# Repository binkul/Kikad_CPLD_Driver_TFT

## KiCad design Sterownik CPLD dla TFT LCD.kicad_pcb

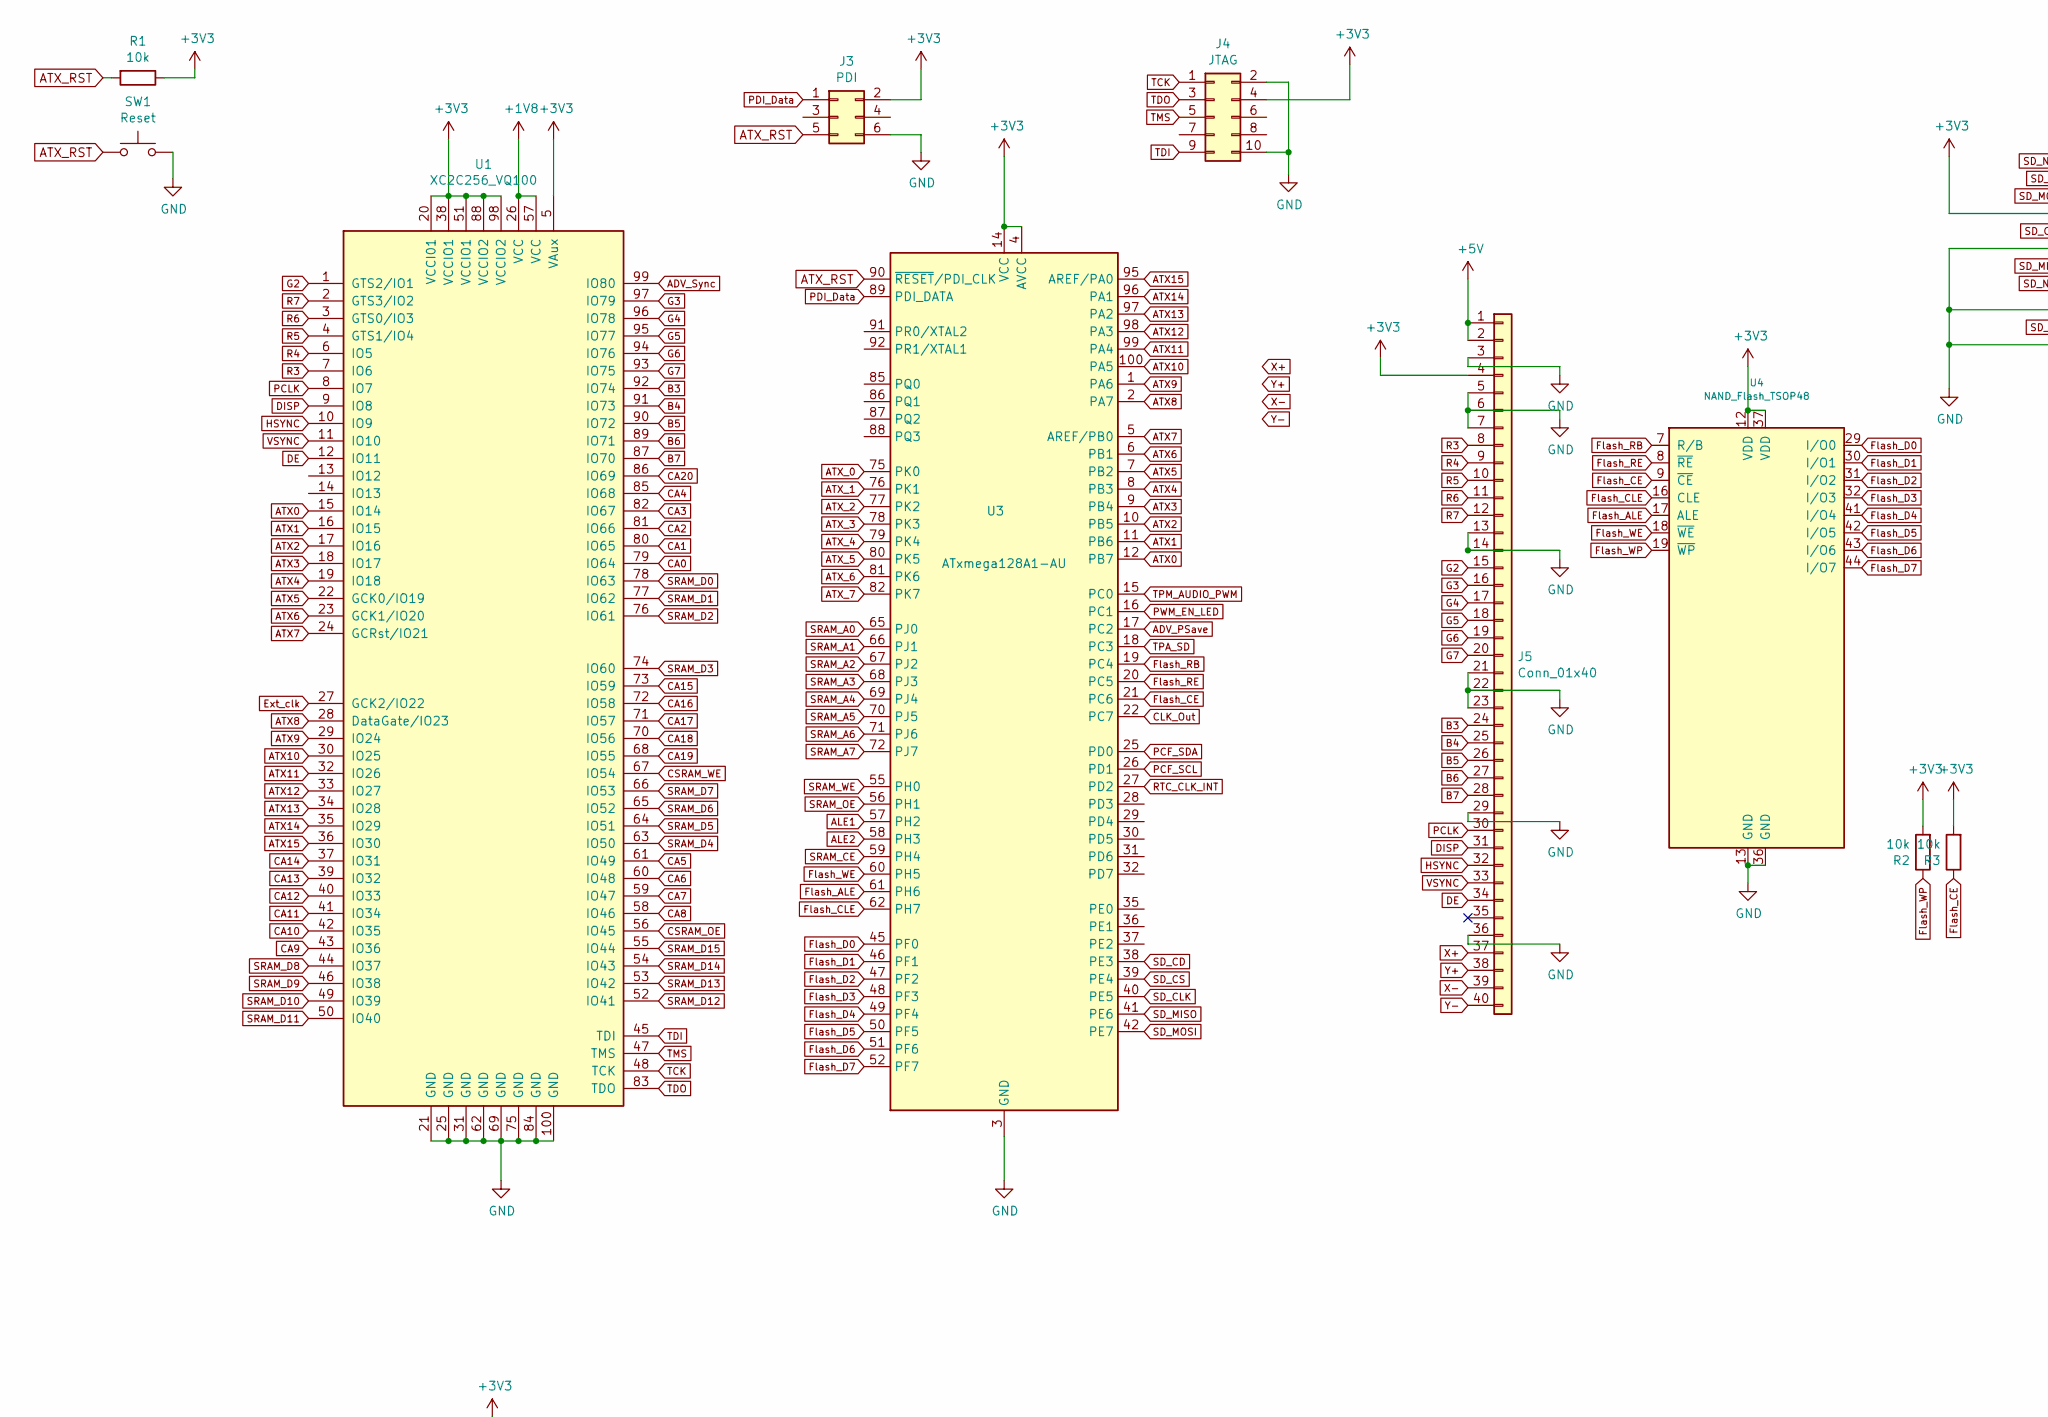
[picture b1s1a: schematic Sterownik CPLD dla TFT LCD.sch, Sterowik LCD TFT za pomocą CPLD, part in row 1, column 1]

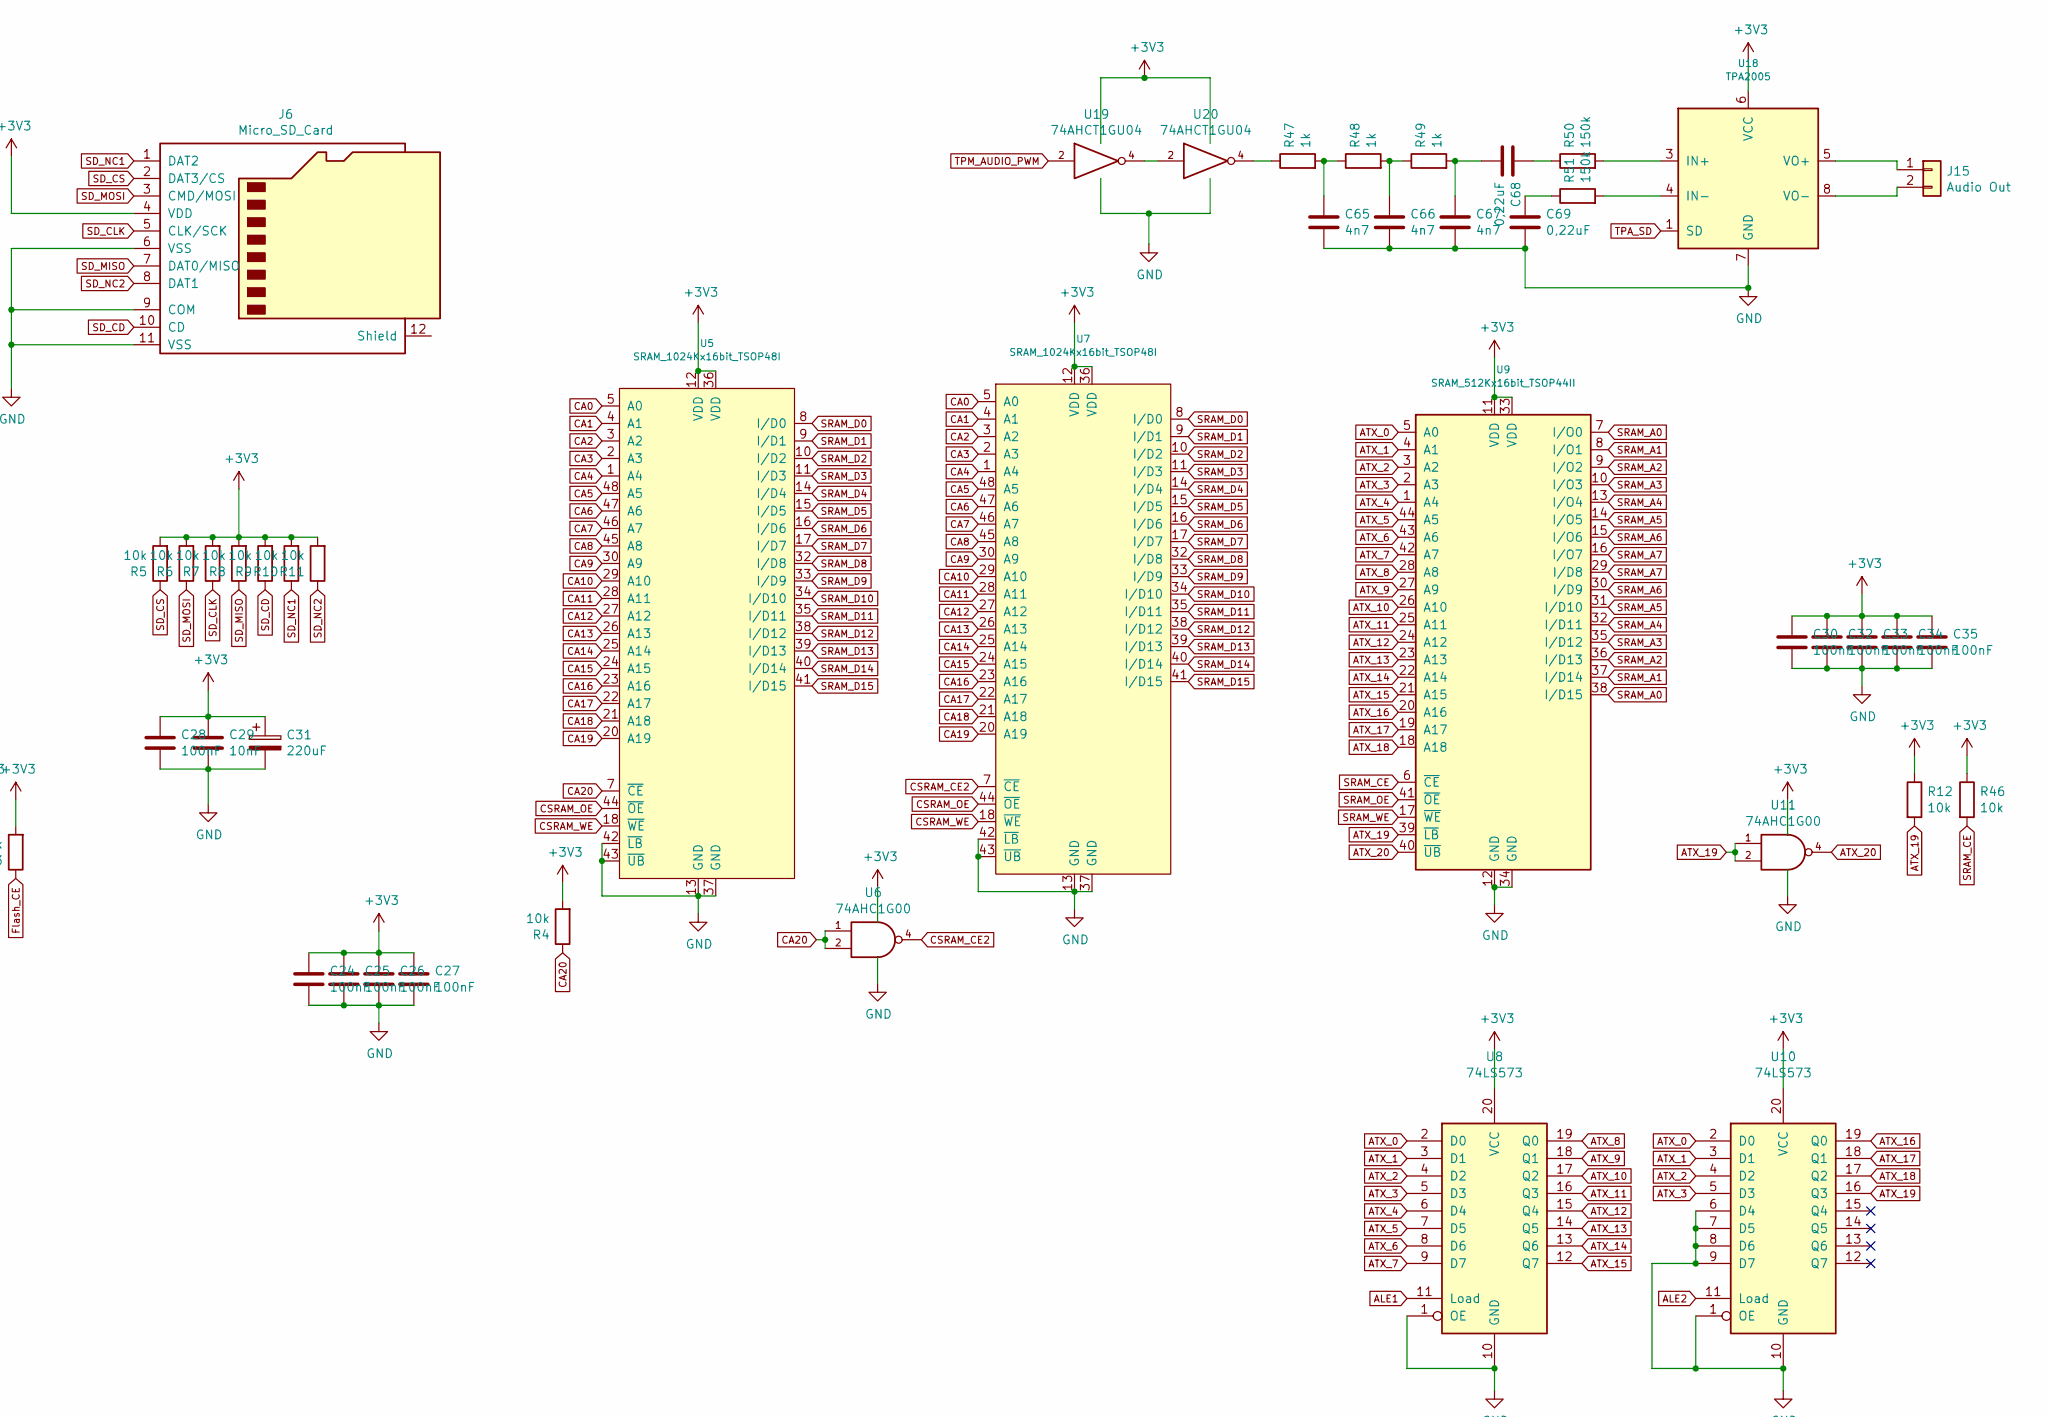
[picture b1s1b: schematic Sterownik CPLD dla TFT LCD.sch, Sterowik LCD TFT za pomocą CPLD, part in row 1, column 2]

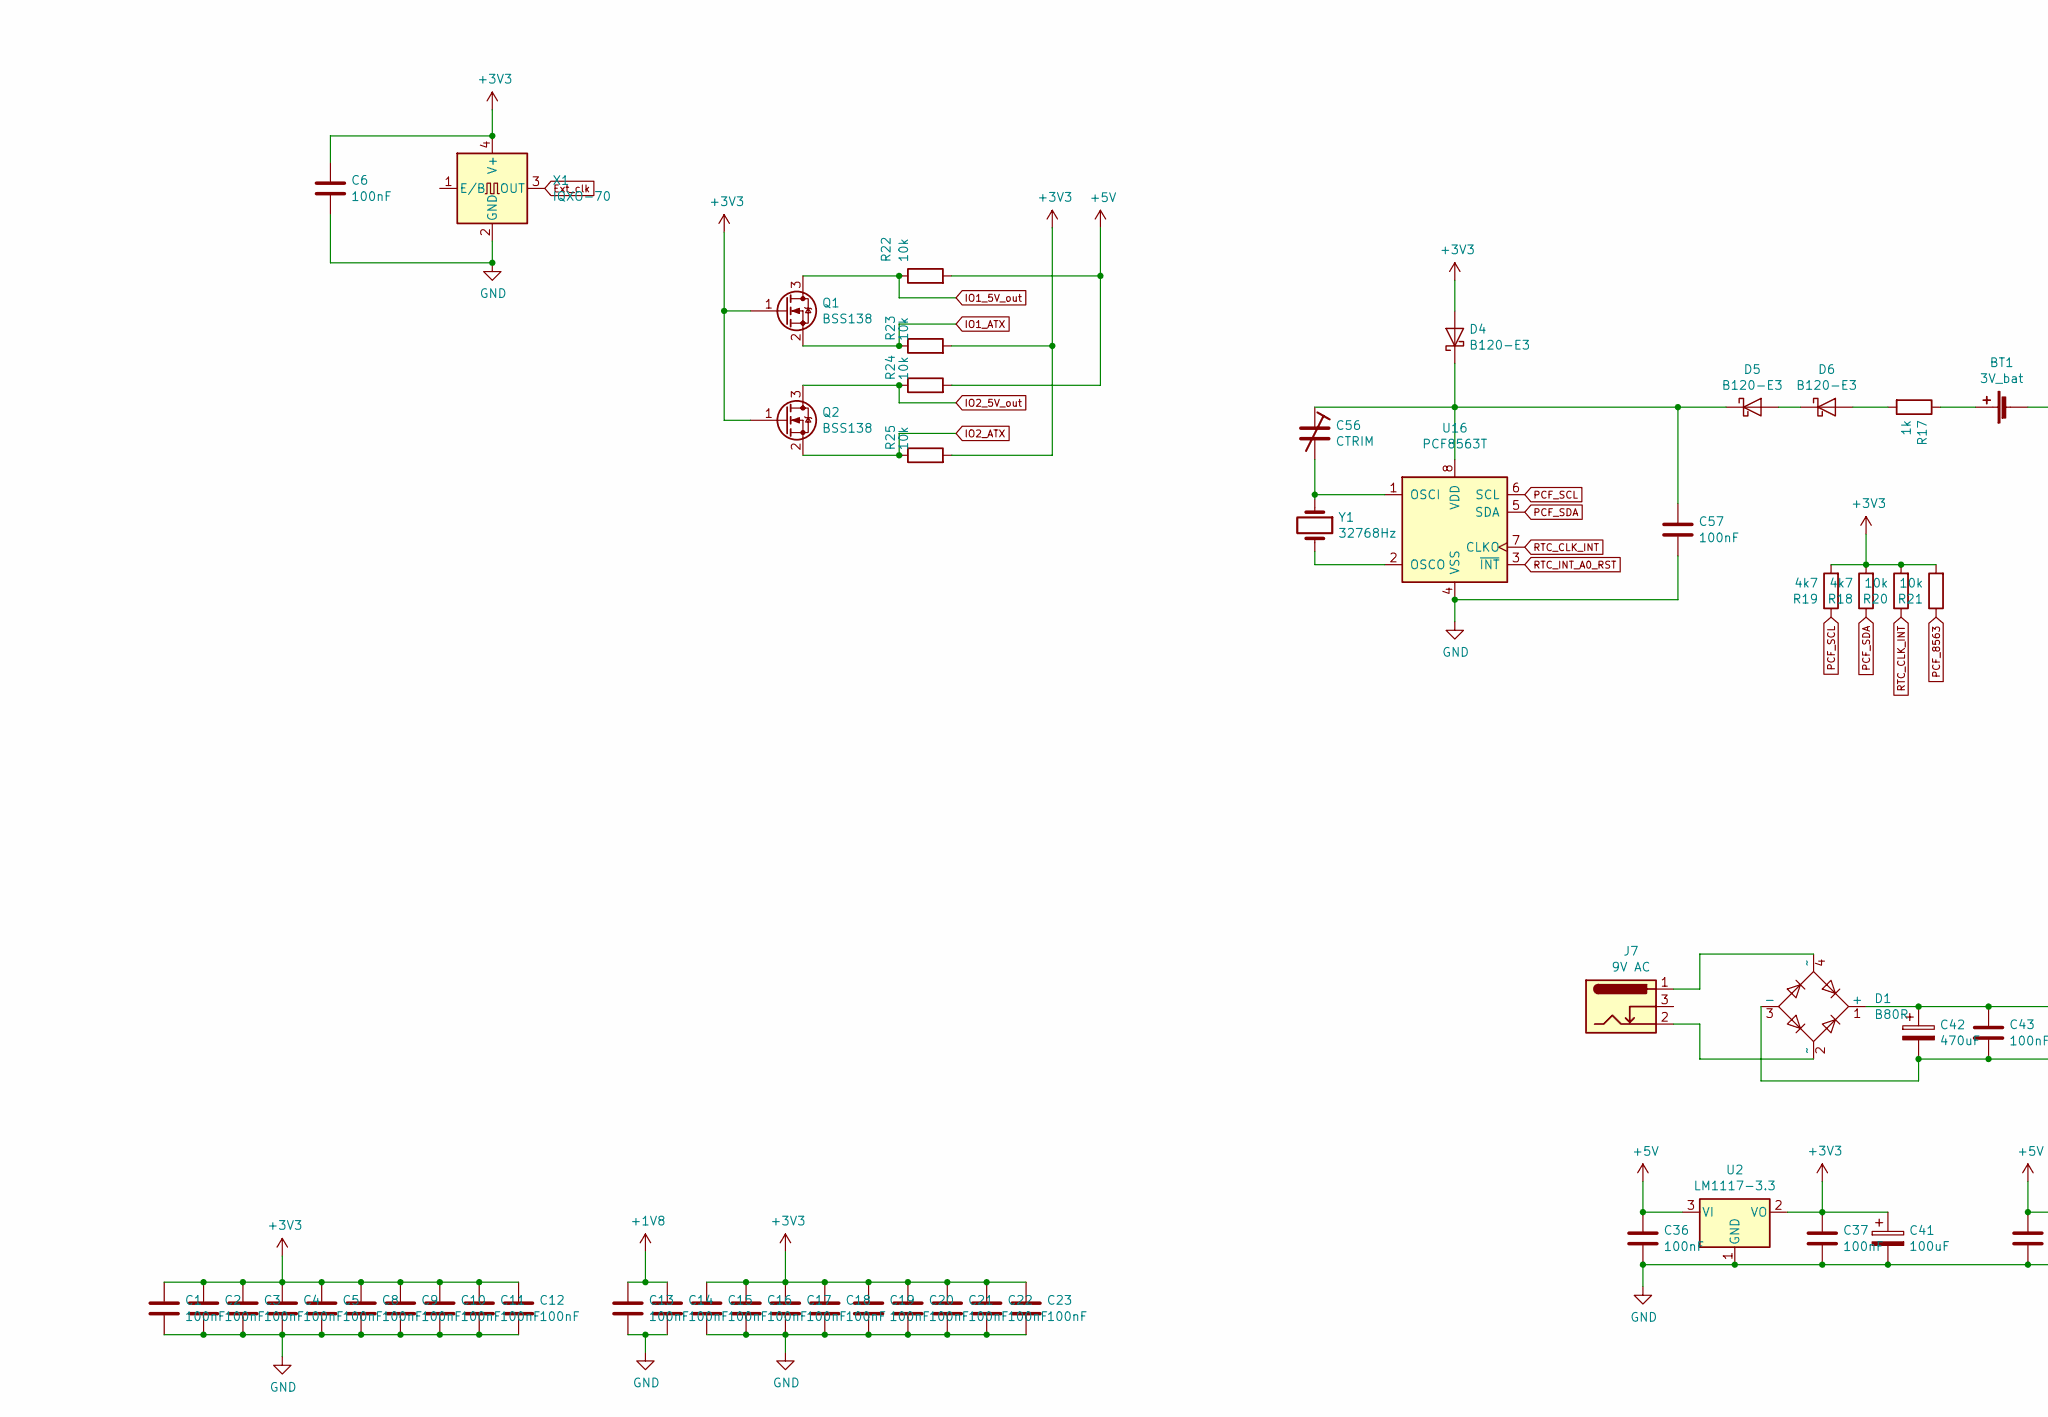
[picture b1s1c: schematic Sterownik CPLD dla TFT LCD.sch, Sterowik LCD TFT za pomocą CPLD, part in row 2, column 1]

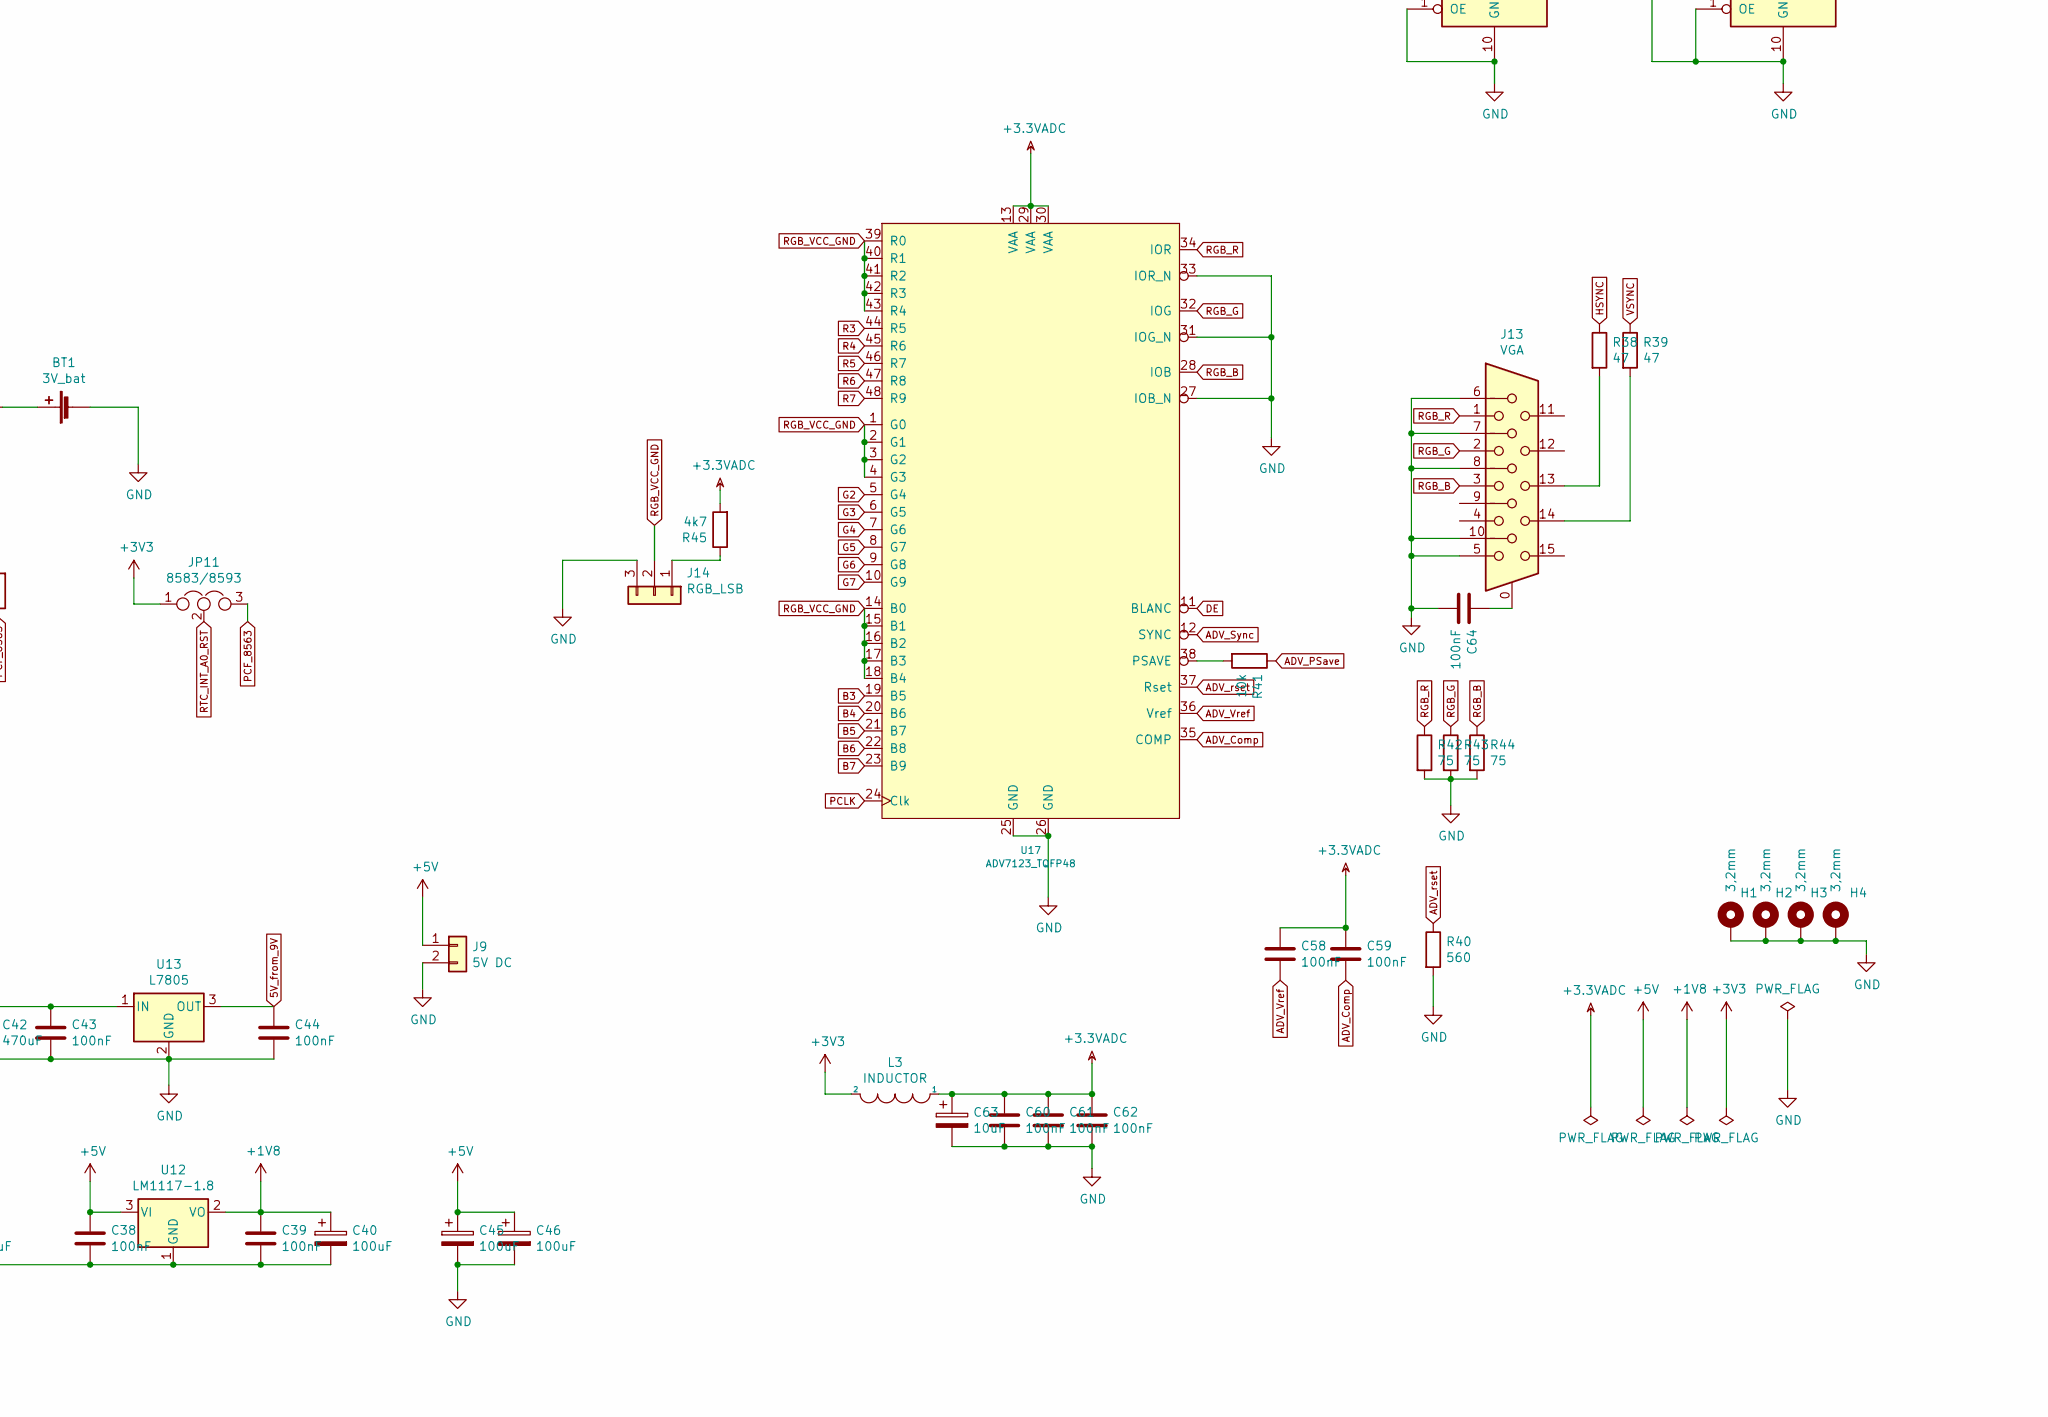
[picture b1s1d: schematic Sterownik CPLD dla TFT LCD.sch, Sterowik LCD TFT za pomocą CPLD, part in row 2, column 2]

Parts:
BT1: 3V_bat; BatteryHolder_CR1220
C1, C2, C3, C4, C5, C8, C9, C10, C11, C12, C13, C14, C15, C16, C17, C18, C19, C20, C21, C22, C23, C24, C25, C26, C27, C28, C30, C32, C33, C34, C35, C57, C58, C59, C60, C61, C62, C64: 100nF; C_0603_1608Metric
C6, C36, C37, C38, C39, C43, C44: 100nF; C_1206_3216Metric
C29: 10nF; C_0603_1608Metric
C31: 220uF; CP_EIA-7343-40_Kemet-Y_Pad2.25x2.55mm_HandSolder
C40, C41, C45, C46: 100uF; CP_Elec_6.3x5.9
C42: 470uF; CP_Radial_D10.0mm_P5.00mm
C56: CTRIM; C_Trimmer_Murata_TZW4
C63: 10uF; CP_Elec_4x3
C65, C66, C67: 4n7; C_0603_1608Metric
C68, C69: 0,22uF; C_1206_3216Metric
D1: B80R; Diode_Bridge_Round_D9.0mm
D4, D5, D6: B120-E3; D_1206_3216Metric
H1, H2, H3, H4: 3,2mm; MountingHole_3.2mm_M3_Pad
J3: PDI; IDC-Header_2x03_P2.54mm_Vertical
J4: JTAG; IDC-Header_2x05_P2.54mm_Vertical
J5: Conn_01x40; Hirose_FH12-40S-0.5SH_1x40-1MP_P0.50mm_Horizontal
J6: Micro_SD_Card; MCC SDMicro
J7: 9V AC; DC_Jack_14mm
J9: 5V DC; Zlacze_srubowe_2x_5mm
J13: VGA; DSUB-15-HD_Female_Horizontal_P2.29x1.98mm_EdgePinOffset8.35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
J14: RGB_LSB; PinHeader_1x03_P2.54mm_Vertical
J15: Audio Out; PinSocket_1x02_P2.54mm_Vertical
JP11: 8583/8593; SolderJumper-3_P1.3mm_Open_RoundedPad1.0x1.5mm
L3: INDUCTOR; L_0805_2012Metric
Q1, Q2: BSS138; SOT-23
R1, R2, R3, R4, R5, R6, R7, R8, R9, R10, R11, R12, R22, R23, R24, R25, R46: 10k; R_0603_1608Metric
R17: 1k; R_1206_3216Metric
R18, R19, R45: 4k7; R_1206_3216Metric
R20, R21: 10k; R_1206_3216Metric
R38, R39: 47; R_0805_2012Metric
R40: 560; R_0805_2012Metric
R41: 10k; R_0805_2012Metric
R42, R43, R44: 75; R_0805_2012Metric
R47, R48, R49: 1k; R_0603_1608Metric
R50, R51: 150k; R_1206_3216Metric
SW1: Reset; MicroSwitch
U1: XC2C256_VQ100; VQFP-100_14x14mm_P0.5mm
U2: LM1117-3.3; TO-252-2
U3: ATxmega128A1-AU; TQFP-100_14x14mm_P0.5mm
U4: NAND_Flash_TSOP48; TSOP-I-48_18.4x12mm_P0.5mm
U5, U7: SRAM_1024Kx16bit_TSOP48I; TSOP-I-48_18.4x12mm_P0.5mm
U6, U11: 74AHC1G00; SOT-23-5
U8, U10: 74LS573; SSOP-20_5.3x7.2mm_P0.65mm
U9: SRAM_512Kx16bit_TSOP44II; TSOP-II-44_10.16x18.41mm_P0.8mm
U12: LM1117-1.8; TO-252-2
U13: L7805; TO-263-2
U16: PCF8563T; SO-8_3.9x4.9mm_P1.27mm
U17: ADV7123_TQFP48; TQFP-48_7x7mm_P0.5mm
U18: TPA2005; MSOP8
U19, U20: 74AHCT1GU04; SOT-23-5
X1: IQXO-70; Oscillator_SMD_IQD_IQXO70-4Pin_7.5x5.0mm
Y1: 32768Hz; Crystal_C26-LF_D2.1mm_L6.5mm_Horizontal

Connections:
5V_from_9V: C44.1, U13.3 (OUT)
+1V8: C13.1, C14.1, C39.1, C40.1, U1.26 (VCC), U1.57 (VCC), U12.2 (VO)
+3.3VADC: C58.1, C59.1, C60.1, C61.1, C62.1, C63.1, L3.1, R45.2, U17.13 (VAA), U17.29 (VAA), U17.30 (VAA)
+3V3: C1.1, C2.1, C3.1, C4.1, C5.1, C6.1, C8.1, C9.1, C10.1, C11.1, C12.1, C15.1, C16.1, C17.1, C18.1, C19.1, C20.1, C21.1, C22.1, C23.1, C24.1, C25.1, C26.1, C27.1, C28.1, C29.1, C30.1, C31.1, C32.1, C33.1, C34.1, C35.1, C37.1, C41.1, D4.2 (A), J3.2, J4.4, J5.4, J6.4 (VDD), JP11.1, L3.2, Q1.1 (G), Q2.1 (G), R1.1, R2.2, R3.2, R4.2, R5.2, R6.2, R7.2, R8.2, R9.2, R10.2, R11.2, R12.1, R18.2, R19.2, R20.2, R21.2, R23.2, R25.2, R46.1, U1.5 (VAux), U1.20 (VCCI01), U1.38 (VCCIO1), U1.51 (VCCIO1), U1.88 (VCCIO2), U1.98 (VCCIO2), U2.2 (VO), U3.4 (AVCC), U3.14 (VCC), U3.24 (VCC), U3.34 (VCC), U3.44 (VCC), U3.54 (VCC), U3.64 (VCC), U3.74 (VCC), U3.83 (VCC), U3.94 (AVCC), U4.12 (VDD), U4.37 (VDD), U5.12 (VDD), U5.36 (VDD), U6.5 (VCC), U7.12 (VDD), U7.36 (VDD), U8.20 (VCC), U9.11 (VDD), U9.33 (VDD), U10.20 (VCC), U11.5 (VCC), U18.6 (VCC), U19.5 (VCC), U20.5 (VCC), X1.4 (V+)
+5V: C36.1, C38.1, C45.1, C46.1, J5.1, J5.2, J9.1, R22.2, R24.2, U2.3 (VI), U12.3 (VI)
ADV_Comp: C59.2, U17.35 (COMP)
ADV_PSave: R41.1, U3.17 (PC2)
ADV_Sync: U1.99 (IO80), U17.12 (SYNC)
ADV_Vref: C58.2, U17.36 (Vref)
ADV_rset: R40.1, U17.37 (Rset)
ALE1: U3.57 (PH2), U8.11 (Load)
ALE2: U3.58 (PH3), U10.11 (Load)
ATX0: U1.15 (IO14), U3.12 (PB7)
ATX1: U1.16 (IO15), U3.11 (PB6)
ATX2: U1.17 (IO16), U3.10 (PB5)
ATX3: U1.18 (IO17), U3.9 (PB4)
ATX4: U1.19 (IO18), U3.8 (PB3)
ATX5: U1.22 (GCK0/IO19), U3.7 (PB2)
ATX6: U1.23 (GCK1/IO20), U3.6 (PB1)
ATX7: U1.24 (GCRst/IO21), U3.5 (AREF/PB0)
ATX8: U1.28 (DataGate/IO23), U3.2 (PA7)
ATX9: U1.29 (IO24), U3.1 (PA6)
ATX10: U1.30 (IO25), U3.100 (PA5)
ATX11: U1.32 (IO26), U3.99 (PA4)
ATX12: U1.33 (IO27), U3.98 (PA3)
ATX13: U1.34 (IO28), U3.97 (PA2)
ATX14: U1.35 (IO29), U3.96 (PA1)
ATX15: U1.36 (IO30), U3.95 (AREF/PA0)
ATX_0: U3.75 (PK0), U8.2 (D0), U9.5 (A0), U10.2 (D0)
ATX_1: U3.76 (PK1), U8.3 (D1), U9.4 (A1), U10.3 (D1)
ATX_2: U3.77 (PK2), U8.4 (D2), U9.3 (A2), U10.4 (D2)
ATX_3: U3.78 (PK3), U8.5 (D3), U9.2 (A3), U10.5 (D3)
ATX_4: U3.79 (PK4), U8.6 (D4), U9.1 (A4)
ATX_5: U3.80 (PK5), U8.7 (D5), U9.44 (A5)
ATX_6: U3.81 (PK6), U8.8 (D6), U9.43 (A6)
ATX_7: U3.82 (PK7), U8.9 (D7), U9.42 (A7)
ATX_8: U8.19 (Q0), U9.28 (A8)
ATX_9: U8.18 (Q1), U9.27 (A9)
ATX_10: U8.17 (Q2), U9.26 (A10)
ATX_11: U8.16 (Q3), U9.25 (A11)
ATX_12: U8.15 (Q4), U9.24 (A12)
ATX_13: U8.14 (Q5), U9.23 (A13)
ATX_14: U8.13 (Q6), U9.22 (A14)
ATX_15: U8.12 (Q7), U9.21 (A15)
ATX_16: U9.20 (A16), U10.19 (Q0)
ATX_17: U9.19 (A17), U10.18 (Q1)
ATX_18: U9.18 (A18), U10.17 (Q2)
ATX_19: R12.2, U9.39 (~LB), U10.16 (Q3), U11.1, U11.2
ATX_20: U9.40 (~UB), U11.4
ATX_RST: J3.5, R1.2, SW1.1, U3.90 (~RESET~/PDI_CLK)
B3: J5.24, U1.92 (IO74), U17.19 (B5)
B4: J5.25, U1.91 (IO73), U17.20 (B6)
B5: J5.26, U1.90 (IO72), U17.21 (B7)
B6: J5.27, U1.89 (IO71), U17.22 (B8)
B7: J5.28, U1.87 (IO70), U17.23 (B9)
CA0: U1.79 (IO64), U5.5 (A0), U7.5 (A0)
CA1: U1.80 (IO65), U5.4 (A1), U7.4 (A1)
CA2: U1.81 (IO66), U5.3 (A2), U7.3 (A2)
CA3: U1.82 (IO67), U5.2 (A3), U7.2 (A3)
CA4: U1.85 (IO68), U5.1 (A4), U7.1 (A4)
CA5: U1.61 (IO49), U5.48 (A5), U7.48 (A5)
CA6: U1.60 (IO48), U5.47 (A6), U7.47 (A6)
CA7: U1.59 (IO47), U5.46 (A7), U7.46 (A7)
CA8: U1.58 (IO46), U5.45 (A8), U7.45 (A8)
CA9: U1.43 (IO36), U5.30 (A9), U7.30 (A9)
CA10: U1.42 (IO35), U5.29 (A10), U7.29 (A10)
CA11: U1.41 (IO34), U5.28 (A11), U7.28 (A11)
CA12: U1.40 (IO33), U5.27 (A12), U7.27 (A12)
CA13: U1.39 (IO32), U5.26 (A13), U7.26 (A13)
CA14: U1.37 (IO31), U5.25 (A14), U7.25 (A14)
CA15: U1.73 (IO59), U5.24 (A15), U7.24 (A15)
CA16: U1.72 (IO58), U5.23 (A16), U7.23 (A16)
CA17: U1.71 (IO57), U5.22 (A17), U7.22 (A17)
CA18: U1.70 (IO56), U5.21 (A18), U7.21 (A18)
CA19: U1.68 (IO55), U5.20 (A19), U7.20 (A19)
CA20: R4.1, U1.86 (IO69), U5.7 (~CE), U6.1, U6.2
CSRAM_CE2: U6.4, U7.7 (~CE)
CSRAM_OE: U1.56 (IO45), U5.44 (~OE), U7.44 (~OE)
CSRAM_WE: U1.67 (IO54), U5.18 (~WE), U7.18 (~WE)
DE: J5.34, U1.12 (IO11), U17.11 (BLANC)
DISP: J5.31, U1.9 (IO8)
Ext_clk: U1.27 (GCK2/IO22), X1.3 (OUT)
Flash_ALE: U3.61 (PH6), U4.17 (ALE)
Flash_CE: R3.1, U3.21 (PC6), U4.9 (~CE)
Flash_CLE: U3.62 (PH7), U4.16 (CLE)
Flash_D0: U3.45 (PF0), U4.29 (I/O0)
Flash_D1: U3.46 (PF1), U4.30 (I/O1)
Flash_D2: U3.47 (PF2), U4.31 (I/O2)
Flash_D3: U3.48 (PF3), U4.32 (I/O3)
Flash_D4: U3.49 (PF4), U4.41 (I/O4)
Flash_D5: U3.50 (PF5), U4.42 (I/O5)
Flash_D6: U3.51 (PF6), U4.43 (I/O6)
Flash_D7: U3.52 (PF7), U4.44 (I/O7)
Flash_RB: U3.19 (PC4), U4.7 (R/B)
Flash_RE: U3.20 (PC5), U4.8 (~RE)
Flash_WE: U3.60 (PH5), U4.18 (~WE)
Flash_WP: R2.1, U4.19 (~WP)
G2: J5.15, U1.1 (GTS2/IO1), U17.5 (G4)
G3: J5.16, U1.97 (IO79), U17.6 (G5)
G4: J5.17, U1.96 (IO78), U17.7 (G6)
G5: J5.18, U1.95 (IO77), U17.8 (G7)
G6: J5.19, U1.94 (IO76), U17.9 (G8)
G7: J5.20, U1.93 (IO75), U17.10 (G9)
GND: BT1.2 (-), C1.2, C2.2, C3.2, C4.2, C5.2, C6.2, C8.2, C9.2, C10.2, C11.2, C12.2, C13.2, C14.2, C15.2, C16.2, C17.2, C18.2, C19.2, C20.2, C21.2, C22.2, C23.2, C24.2, C25.2, C26.2, C27.2, C28.2, C29.2, C30.2, C31.2, C32.2, C33.2, C34.2, C35.2, C36.2, C37.2, C38.2, C39.2, C40.2, C41.2, C42.2, C43.2, C44.2, C45.2, C46.2, C57.2, C60.2, C61.2, C62.2, C63.2, C64.2, C65.2, C66.2, C67.2, C69.2, D1.3 (-), H1.1, H2.1, H3.1, H4.1, J3.6, J4.2, J4.10, J5.3, J5.5, J5.6, J5.7, J5.13, J5.14, J5.21, J5.22, J5.23, J5.29, J5.36, J6.6 (VSS), J6.9 (COM), J6.11 (VSS), J9.2, J13.5, J13.6, J13.7, J13.8, J13.10, J14.3, R40.2, R42.2, R43.2, R44.2, SW1.2, U1.21 (GND), U1.25 (GND), U1.31 (GND), U1.62 (GND), U1.69 (GND), U1.75 (GND), U1.84 (GND), U1.100 (GND), U2.1 (GND), U3.3 (GND), U3.13 (GND), U3.23 (GND), U3.33 (GND), U3.43 (GND), U3.53 (GND), U3.63 (GND), U3.73 (GND), U3.84 (GND), U3.93 (GND), U4.13 (GND), U4.36 (GND), U5.13 (GND), U5.37 (GND), U5.42 (~LB), U5.43 (~UB), U6.3 (GND), U7.13 (GND), U7.37 (GND), U7.42 (~LB), U7.43 (~UB), U8.1 (OE), U8.10 (GND), U9.12 (GND), U9.34 (GND), U10.1 (OE), U10.6 (D4), U10.7 (D5), U10.8 (D6), U10.9 (D7), U10.10 (GND), U11.3 (GND), U12.1 (GND), U13.2 (GND), U16.4 (VSS), U17.25 (GND), U17.26 (GND), U17.27 (IOB_N), U17.31 (IOG_N), U17.33 (IOR_N), U18.7 (GND), U19.3 (GND), U20.3 (GND), X1.2 (GND)
HSYNC: J5.32, R38.1, U1.10 (IO9)
IO1_5V_out: Q1.3 (D), R22.1
IO1_ATX: Q1.2 (S), R23.1
IO2_5V_out: Q2.3 (D), R24.1
IO2_ATX: Q2.2 (S), R25.1
unnamed: BT1.1 (+), R17.1
unnamed: C42.1, C43.1, D1.1 (+), U13.1 (IN)
unnamed: C56.1, C57.1, D4.1 (K), D5.1 (K), U16.8 (VDD)
unnamed: C56.2, U16.1 (OSCI), Y1.1
unnamed: C64.1, J13.0
unnamed: C65.1, R47.2, R48.1
unnamed: C66.1, R48.2, R49.1
unnamed: C67.1, C68.2, R49.2
unnamed: C68.1, R50.1
unnamed: C69.1, R51.1
unnamed: D1.2 (~~), J7.2
unnamed: D1.4 (~~), J7.1
unnamed: D5.2 (A), D6.1 (K)
unnamed: D6.2 (A), R17.2
unnamed: J13.13, R38.2
unnamed: J13.14, R39.2
unnamed: J14.1, R45.1
unnamed: J15.1, U18.5 (VO+)
unnamed: J15.2, U18.8 (VO-)
unnamed: R41.2, U17.38 (PSAVE)
unnamed: R47.1, U20.4
unnamed: R50.2, U18.3 (IN+)
unnamed: R51.2, U18.4 (IN-)
unnamed: U16.2 (OSCO), Y1.2
unnamed: U19.4, U20.2
PCF_8563: JP11.3, R21.1
PCF_SCL: R19.1, U3.26 (PD1), U16.6 (SCL)
PCF_SDA: R18.1, U3.25 (PD0), U16.5 (SDA)
PCLK: J5.30, U1.8 (IO7), U17.24 (Clk)
PDI_Data: J3.1, U3.89 (PDI_DATA)
R3: J5.8, U1.7 (IO6), U17.44 (R5)
R4: J5.9, U1.6 (IO5), U17.45 (R6)
R5: J5.10, U1.4 (GTS1/IO4), U17.46 (R7)
R6: J5.11, U1.3 (GTS0/IO3), U17.47 (R8)
R7: J5.12, U1.2 (GTS3/IO2), U17.48 (R9)
RGB_B: J13.3, R44.1, U17.28 (IOB)
RGB_G: J13.2, R43.1, U17.32 (IOG)
RGB_R: J13.1, R42.1, U17.34 (IOR)
RGB_VCC_GND: J14.2, U17.1 (G0), U17.2 (G1), U17.3 (G2), U17.4 (G3), U17.14 (B0), U17.15 (B1), U17.16 (B2), U17.17 (B3), U17.18 (B4), U17.39 (R0), U17.40 (R1), U17.41 (R2), U17.42 (R3), U17.43 (R4)
RTC_CLK_INT: R20.1, U3.27 (PD2), U16.7 (CLKO)
RTC_INT_A0_RST: JP11.2, U16.3 (~INT~)
SD_CD: J6.10 (CD), R9.1, U3.38 (PE3)
SD_CLK: J6.5 (CLK/SCK), R7.1, U3.40 (PE5)
SD_CS: J6.2 (DAT3/CS), R5.1, U3.39 (PE4)
SD_MISO: J6.7 (DAT0/MISO), R8.1, U3.41 (PE6)
SD_MOSI: J6.3 (CMD/MOSI), R6.1, U3.42 (PE7)
SD_NC1: J6.1 (DAT2), R10.1
SD_NC2: J6.8 (DAT1), R11.1
SRAM_A0: U3.65 (PJ0), U9.7 (I/O0), U9.38 (I/D15)
SRAM_A1: U3.66 (PJ1), U9.8 (I/O1), U9.37 (I/D14)
SRAM_A2: U3.67 (PJ2), U9.9 (I/O2), U9.36 (I/D13)
SRAM_A3: U3.68 (PJ3), U9.10 (I/O3), U9.35 (I/D12)
SRAM_A4: U3.69 (PJ4), U9.13 (I/O4), U9.32 (I/D11)
SRAM_A5: U3.70 (PJ5), U9.14 (I/O5), U9.31 (I/D10)
SRAM_A6: U3.71 (PJ6), U9.15 (I/O6), U9.30 (I/D9)
SRAM_A7: U3.72 (PJ7), U9.16 (I/O7), U9.29 (I/D8)
SRAM_CE: R46.2, U3.59 (PH4), U9.6 (~CE)
SRAM_D0: U1.78 (IO63), U5.8 (I/D0), U7.8 (I/D0)
SRAM_D1: U1.77 (IO62), U5.9 (I/D1), U7.9 (I/D1)
SRAM_D2: U1.76 (IO61), U5.10 (I/D2), U7.10 (I/D2)
SRAM_D3: U1.74 (IO60), U5.11 (I/D3), U7.11 (I/D3)
SRAM_D4: U1.63 (IO50), U5.14 (I/D4), U7.14 (I/D4)
SRAM_D5: U1.64 (IO51), U5.15 (I/D5), U7.15 (I/D5)
SRAM_D6: U1.65 (IO52), U5.16 (I/D6), U7.16 (I/D6)
SRAM_D7: U1.66 (IO53), U5.17 (I/D7), U7.17 (I/D7)
SRAM_D8: U1.44 (IO37), U5.32 (I/D8), U7.32 (I/D8)
SRAM_D9: U1.46 (IO38), U5.33 (I/D9), U7.33 (I/D9)
SRAM_D10: U1.49 (IO39), U5.34 (I/D10), U7.34 (I/D10)
SRAM_D11: U1.50 (IO40), U5.35 (I/D11), U7.35 (I/D11)
SRAM_D12: U1.52 (IO41), U5.38 (I/D12), U7.38 (I/D12)
SRAM_D13: U1.53 (IO42), U5.39 (I/D13), U7.39 (I/D13)
SRAM_D14: U1.54 (IO43), U5.40 (I/D14), U7.40 (I/D14)
SRAM_D15: U1.55 (IO44), U5.41 (I/D15), U7.41 (I/D15)
SRAM_OE: U3.56 (PH1), U9.41 (~OE)
SRAM_WE: U3.55 (PH0), U9.17 (~WE)
TCK: J4.1, U1.48 (TCK)
TDI: J4.9, U1.45 (TDI)
TDO: J4.3, U1.83 (TDO)
TMS: J4.5, U1.47 (TMS)
TPA_SD: U3.18 (PC3), U18.1 (SD)
TPM_AUDIO_PWM: U3.15 (PC0), U19.2
VSYNC: J5.33, R39.1, U1.11 (IO10)

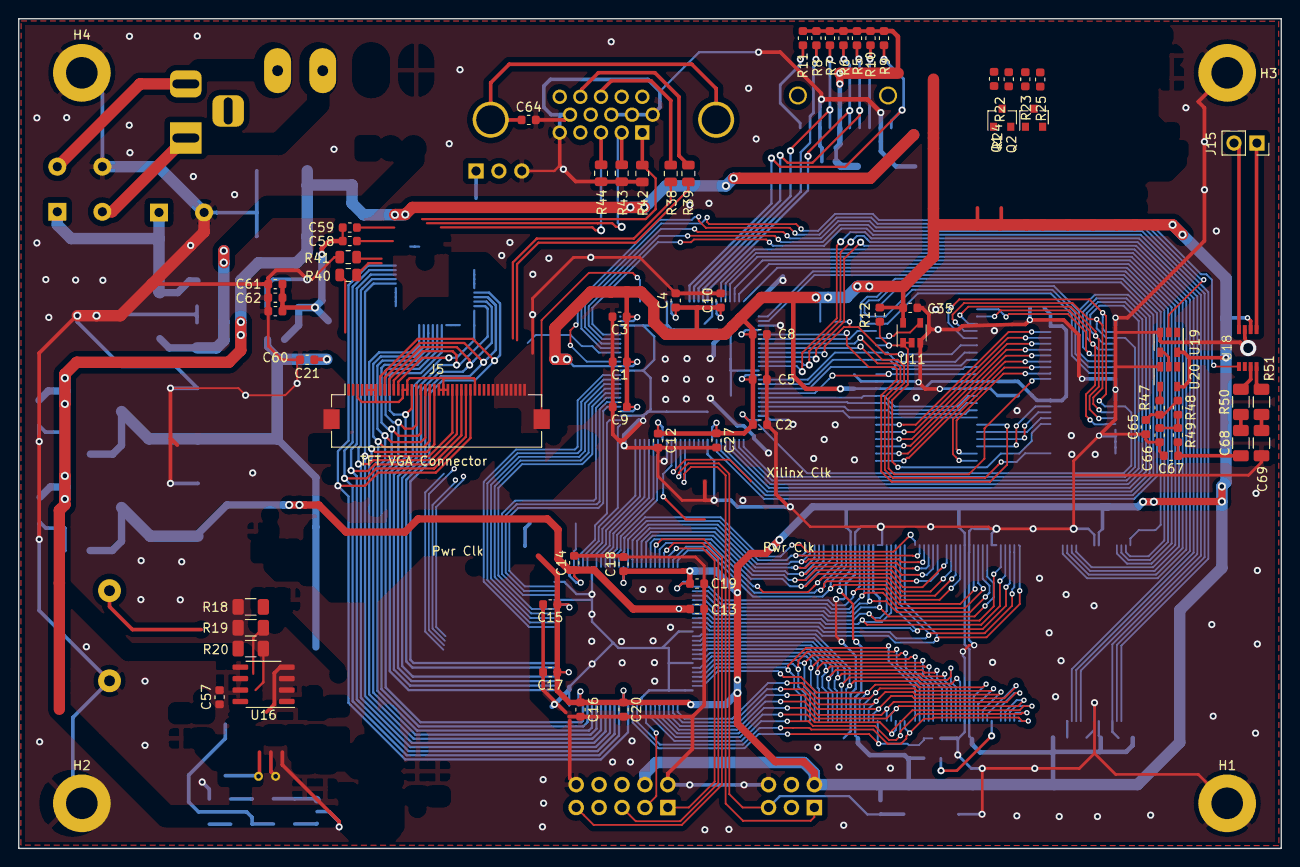
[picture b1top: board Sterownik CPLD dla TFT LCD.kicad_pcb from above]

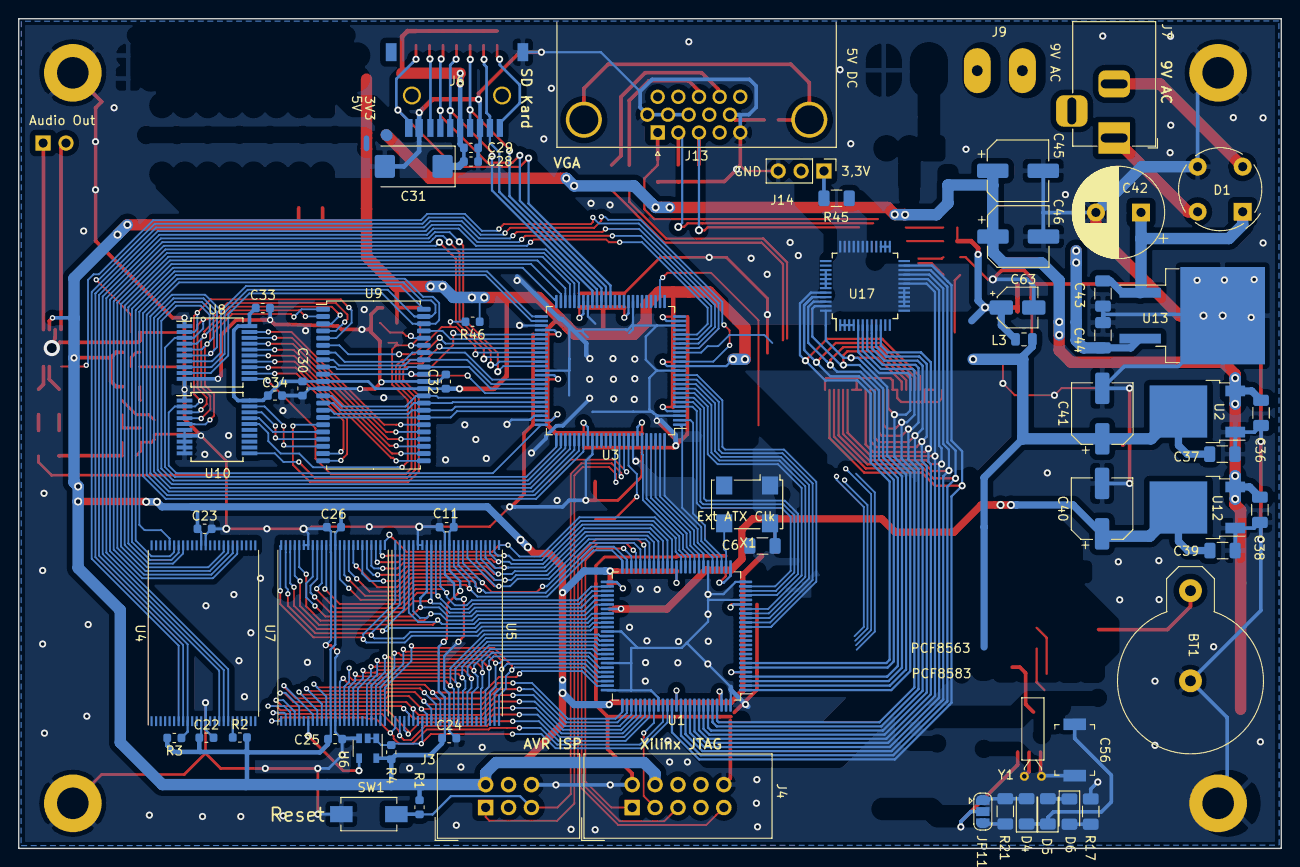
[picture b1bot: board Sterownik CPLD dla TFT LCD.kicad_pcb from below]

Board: 2 copper layers, 140.0 x 92.0 mm, 137 parts (65 on the bottom side), 191 nets.

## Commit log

2024-06-02 I-sze zmiany
